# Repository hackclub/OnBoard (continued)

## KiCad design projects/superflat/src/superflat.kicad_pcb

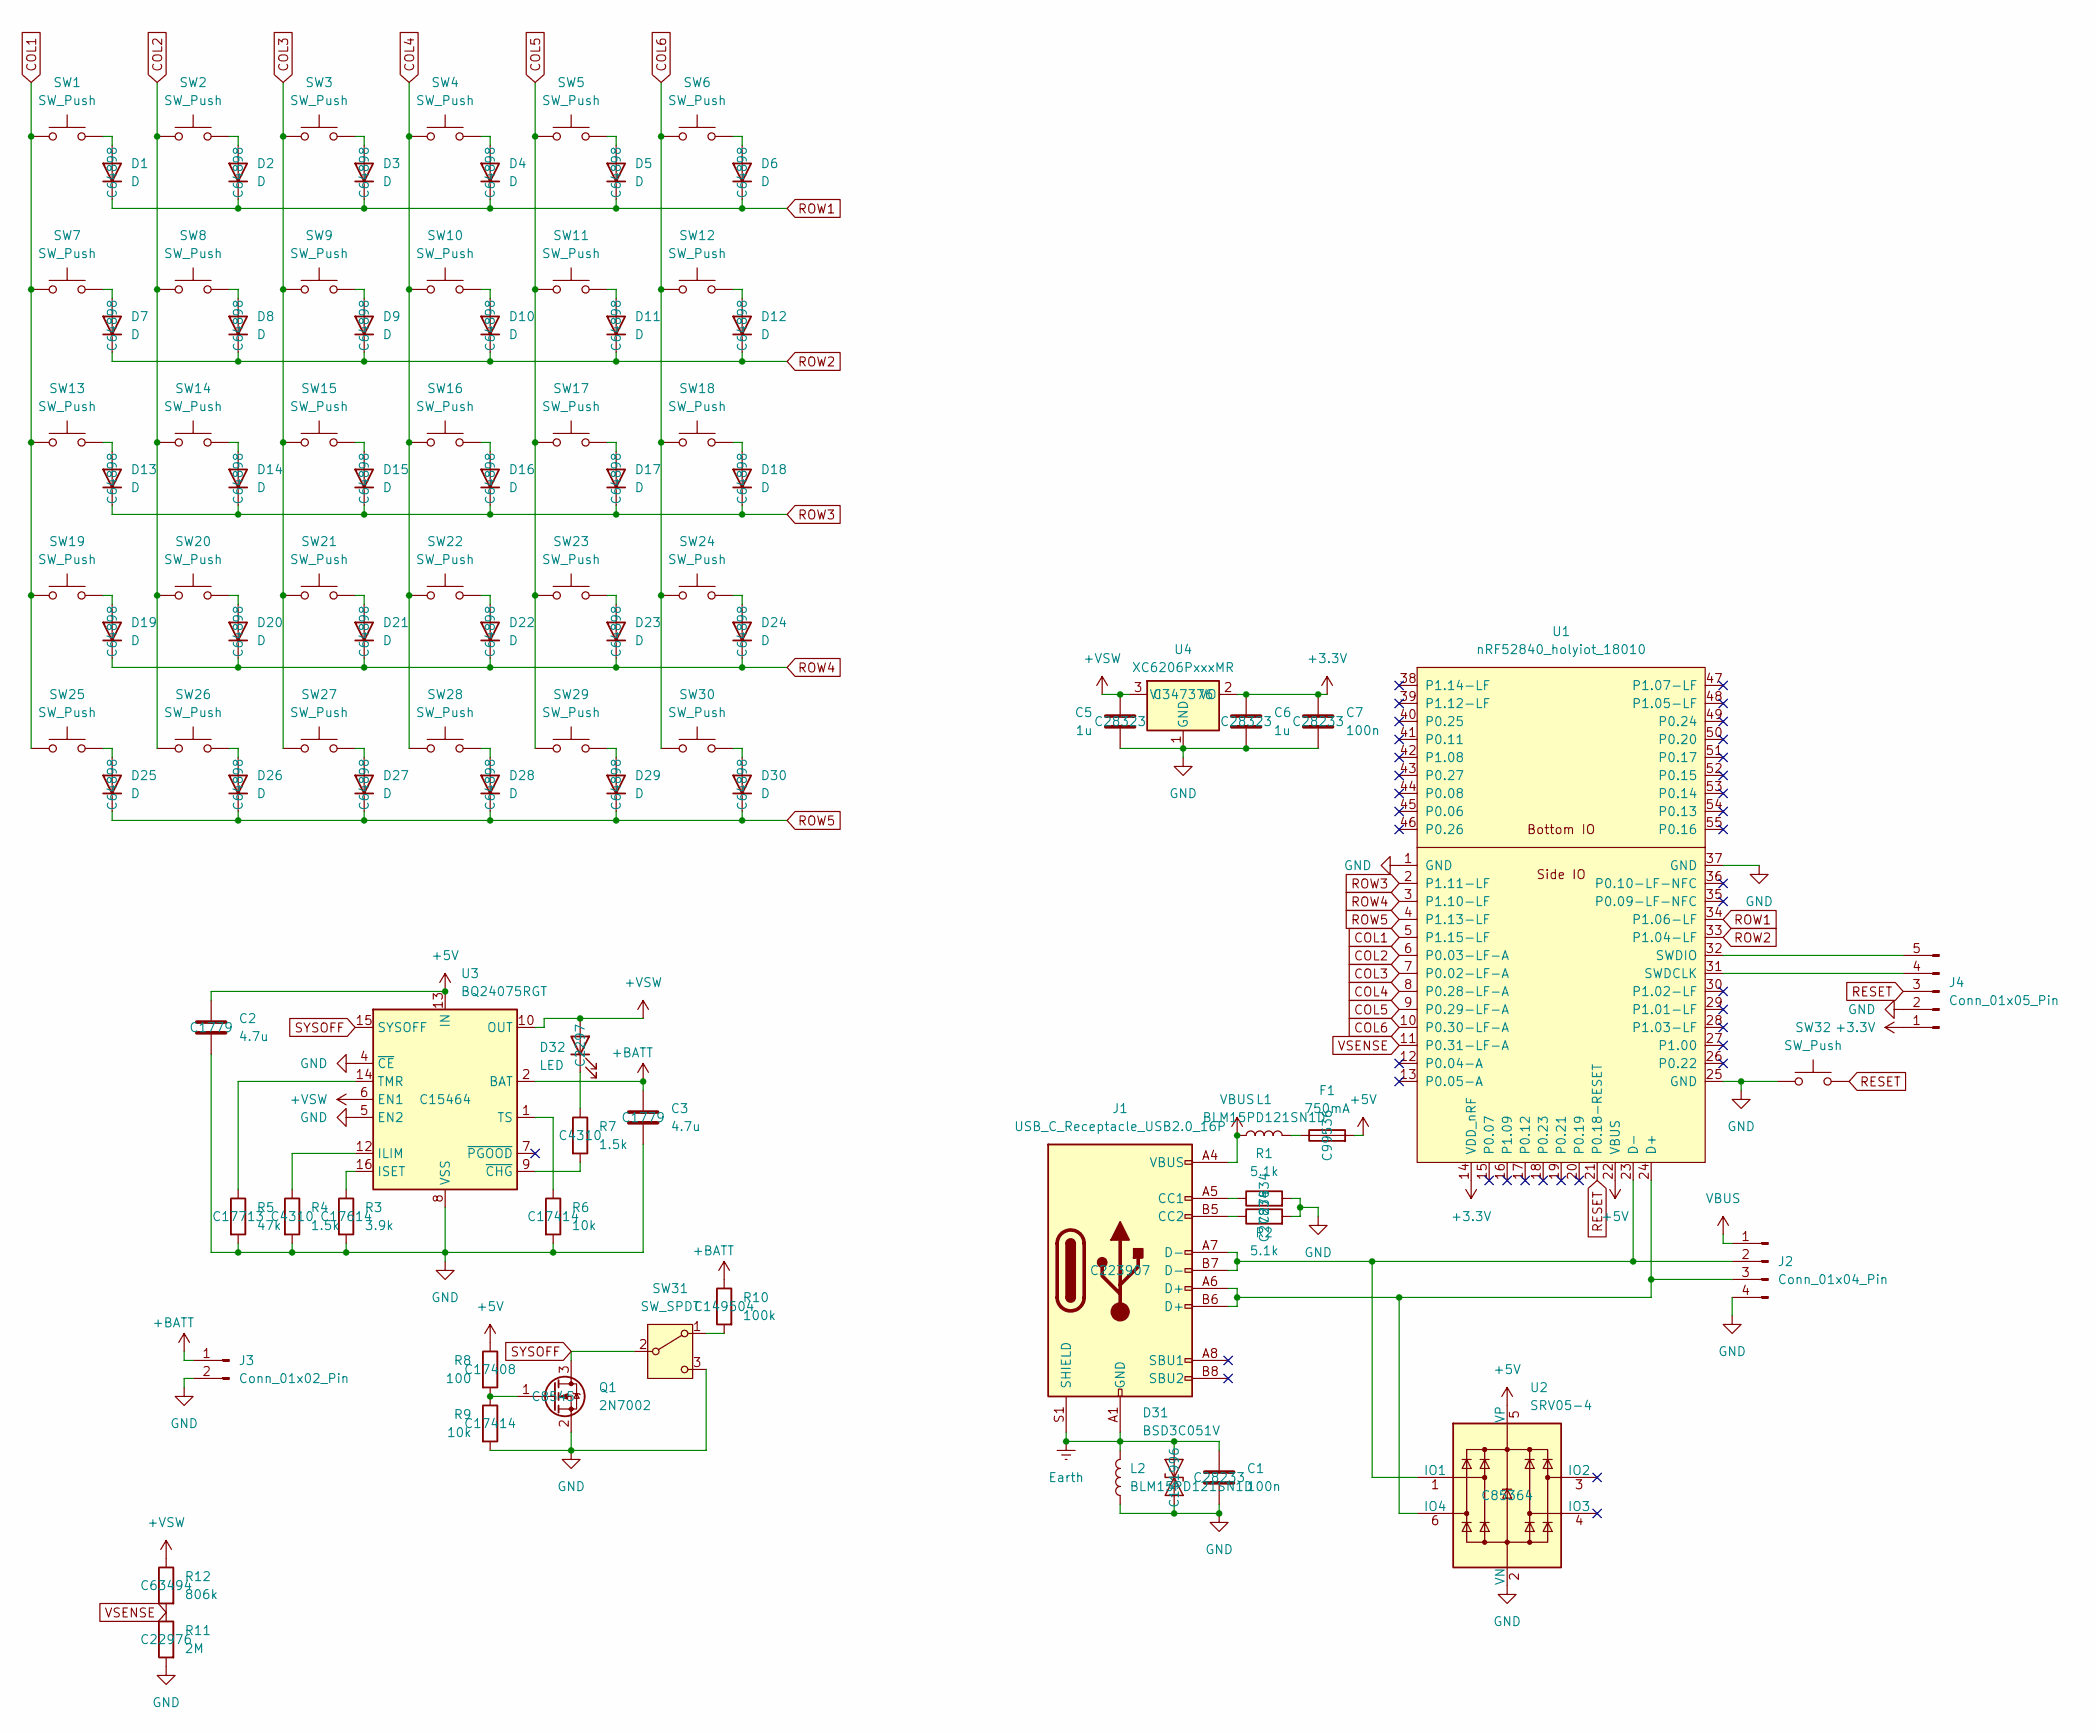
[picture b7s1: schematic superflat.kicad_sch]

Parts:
C1, C7: 100n; C_0805_2012Metric_Pad1.18x1.45mm_HandSolder; LCSC C28233
C2, C3: 4.7u; C_0805_2012Metric_Pad1.18x1.45mm_HandSolder; LCSC C1779
C5, C6: 1u; C_0805_2012Metric_Pad1.18x1.45mm_HandSolder; LCSC C28323
D1, D2, D3, D4, D5, D6, D7, D8, D9, D10, D11, D12, D13, D14, D15, D16, D17, D18, D19, D20, D21, D22, D23, D24, D25, D26, D27, D28, D29, D30: D; D_SOD-123F; LCSC C64898
D31: BSD3C051V; D_SMA; LCSC C151996
D32: LED; LED_0805_2012Metric_Pad1.15x1.40mm_HandSolder; LCSC C2297
F1: 750mA; Fuse_1206_3216Metric_Pad1.42x1.75mm_HandSolder; LCSC C99536
J1: USB_C_Receptacle_USB2.0_16P; USB_C_Receptacle_HRO_TYPE-C-31-M-14; LCSC C223907
J2: Conn_01x04_Pin; PinHeader_1x04_P2.54mm_Vertical
J3: Conn_01x02_Pin; PinHeader_1x02_P2.54mm_Vertical
J4: Conn_01x05_Pin; PinHeader_1x05_P2.54mm_Vertical
L1, L2: BLM15PD121SN1D; L_0402_1005Metric_Pad0.77x0.64mm_HandSolder
Q1: 2N7002; SOT-23; LCSC C8545
R1, R2: 5.1k; R_0805_2012Metric_Pad1.20x1.40mm_HandSolder; LCSC C27834
R3: 3.9k; R_0805_2012Metric_Pad1.20x1.40mm_HandSolder; LCSC C17614
R4, R7: 1.5k; R_0805_2012Metric_Pad1.20x1.40mm_HandSolder; LCSC C4310
R5: 47k; R_0805_2012Metric_Pad1.20x1.40mm_HandSolder; LCSC C17713
R6, R9: 10k; R_0805_2012Metric_Pad1.20x1.40mm_HandSolder; LCSC C17414
R8: 100; R_0805_2012Metric_Pad1.20x1.40mm_HandSolder; LCSC C17408
R10: 100k; R_0805_2012Metric_Pad1.20x1.40mm_HandSolder; LCSC C149504
R11: 2M; R_0603_1608Metric_Pad0.98x0.95mm_HandSolder; LCSC C22976
R12: 806k; R_0805_2012Metric_Pad1.20x1.40mm_HandSolder; LCSC C63494
SW1, SW2, SW3, SW4, SW5, SW6, SW7, SW8, SW9, SW10, SW11, SW12, SW13, SW14, SW15, SW16, SW17, SW18, SW19, SW20, SW21, SW22, SW23, SW24, SW25, SW26, SW27, SW28, SW29, SW30: SW_Push; SW_PG1316S
SW31: SW_SPDT; Slide
SW32: SW_Push; SolderJumper-2_P1.3mm_Open_RoundedPad1.0x1.5mm
U1: nRF52840_holyiot_18010; nRF52840_holyiot_18010_HS_simple
U2: SRV05-4; SOT-23-6-routable; LCSC C85364
U3: BQ24075RGT; VQFN-16-1EP_3x3mm_P0.5mm_EP1.6x1.6mm; LCSC C15464
U4: XC6206PxxxMR; SOT-23-3; LCSC C347376

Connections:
+3.3V: C6.1, C7.1, J4.1, U1.14 (VDD_nRF), U4.2 (VO)
+5V: C2.1, F1.2, R8.1, U1.22 (VBUS), U2.5 (VP), U3.13 (IN)
+BATT: C3.1, J3.1, R10.1, U3.2 (BAT), U3.3 (BAT)
+VSW: C5.1, D32.2 (A), R12.1, U3.6 (EN1), U3.10 (OUT), U3.11 (OUT), U4.3 (VI)
COL1: SW1.1, SW7.1, SW13.1, SW19.1, SW25.1, U1.5 (P1.15-LF)
COL2: SW2.1, SW8.1, SW14.1, SW20.1, SW26.1, U1.6 (P0.03-LF-A)
COL3: SW3.1, SW9.1, SW15.1, SW21.1, SW27.1, U1.7 (P0.02-LF-A)
COL4: SW4.1, SW10.1, SW16.1, SW22.1, SW28.1, U1.8 (P0.28-LF-A)
COL5: SW5.1, SW11.1, SW17.1, SW23.1, SW29.1, U1.9 (P0.29-LF-A)
COL6: SW6.1, SW12.1, SW18.1, SW24.1, SW30.1, U1.10 (P0.30-LF-A)
Earth: C1.1, D31.2 (A2), J1.A1 (GND), J1.A12 (GND), J1.B1 (GND), J1.B12 (GND), J1.S1 (SHIELD), L2.2
GND: C1.2, C2.2, C3.2, C5.2, C6.2, C7.2, D31.1 (A1), J2.4, J3.2, J4.2, L2.1, Q1.2 (S), R1.2, R2.2, R3.2, R4.2, R5.2, R6.2, R9.2, R11.2, SW31.3 (C), SW32.1, U1.1 (GND), U1.25 (GND), U1.37 (GND), U2.2 (VN), U3.4 (~CE), U3.5 (EN2), U3.8 (VSS), U3.17 (VSS), U4.1 (GND)
unnamed: D1.2 (A), SW1.2
unnamed: D2.2 (A), SW2.2
unnamed: D3.2 (A), SW3.2
unnamed: D4.2 (A), SW4.2
unnamed: D5.2 (A), SW5.2
unnamed: D6.2 (A), SW6.2
unnamed: D7.2 (A), SW7.2
unnamed: D8.2 (A), SW8.2
unnamed: D9.2 (A), SW9.2
unnamed: D10.2 (A), SW10.2
unnamed: D11.2 (A), SW11.2
unnamed: D12.2 (A), SW12.2
unnamed: D13.2 (A), SW13.2
unnamed: D14.2 (A), SW14.2
unnamed: D15.2 (A), SW15.2
unnamed: D16.2 (A), SW16.2
unnamed: D17.2 (A), SW17.2
unnamed: D18.2 (A), SW18.2
unnamed: D19.2 (A), SW19.2
unnamed: D20.2 (A), SW20.2
unnamed: D21.2 (A), SW21.2
unnamed: D22.2 (A), SW22.2
unnamed: D23.2 (A), SW23.2
unnamed: D24.2 (A), SW24.2
unnamed: D25.2 (A), SW25.2
unnamed: D26.2 (A), SW26.2
unnamed: D27.2 (A), SW27.2
unnamed: D28.2 (A), SW28.2
unnamed: D29.2 (A), SW29.2
unnamed: D30.2 (A), SW30.2
unnamed: D32.1 (K), R7.1
unnamed: F1.1, L1.2
unnamed: J1.A5 (CC1), R1.1
unnamed: J1.B5 (CC2), R2.1
unnamed: J1.A7 (D-), J1.B7 (D-), J2.2, U1.23 (D-), U2.1 (IO1)
unnamed: J1.A6 (D+), J1.B6 (D+), J2.3, U1.24 (D+), U2.6 (IO4)
unnamed: J4.4, U1.31 (SWDCLK)
unnamed: J4.5, U1.32 (SWDIO)
unnamed: Q1.1 (G), R8.2, R9.1
unnamed: R10.2, SW31.1 (A)
unnamed: R4.1, U3.12 (ILIM)
unnamed: R3.1, U3.16 (ISET)
unnamed: R5.1, U3.14 (TMR)
unnamed: R6.1, U3.1 (TS)
unnamed: R7.2, U3.9 (~CHG)
RESET: J4.3, SW32.2, U1.21 (P0.18-RESET)
ROW1: D1.1 (K), D2.1 (K), D3.1 (K), D4.1 (K), D5.1 (K), D6.1 (K), U1.34 (P1.06-LF)
ROW2: D7.1 (K), D8.1 (K), D9.1 (K), D10.1 (K), D11.1 (K), D12.1 (K), U1.33 (P1.04-LF)
ROW3: D13.1 (K), D14.1 (K), D15.1 (K), D16.1 (K), D17.1 (K), D18.1 (K), U1.2 (P1.11-LF)
ROW4: D19.1 (K), D20.1 (K), D21.1 (K), D22.1 (K), D23.1 (K), D24.1 (K), U1.3 (P1.10-LF)
ROW5: D25.1 (K), D26.1 (K), D27.1 (K), D28.1 (K), D29.1 (K), D30.1 (K), U1.4 (P1.13-LF)
SYSOFF: Q1.3 (D), SW31.2 (B), U3.15 (SYSOFF)
VBUS: J1.A4 (VBUS), J1.A9 (VBUS), J1.B4 (VBUS), J1.B9 (VBUS), J2.1, L1.1
VSENSE: R11.1, R12.2, U1.11 (P0.31-LF-A)

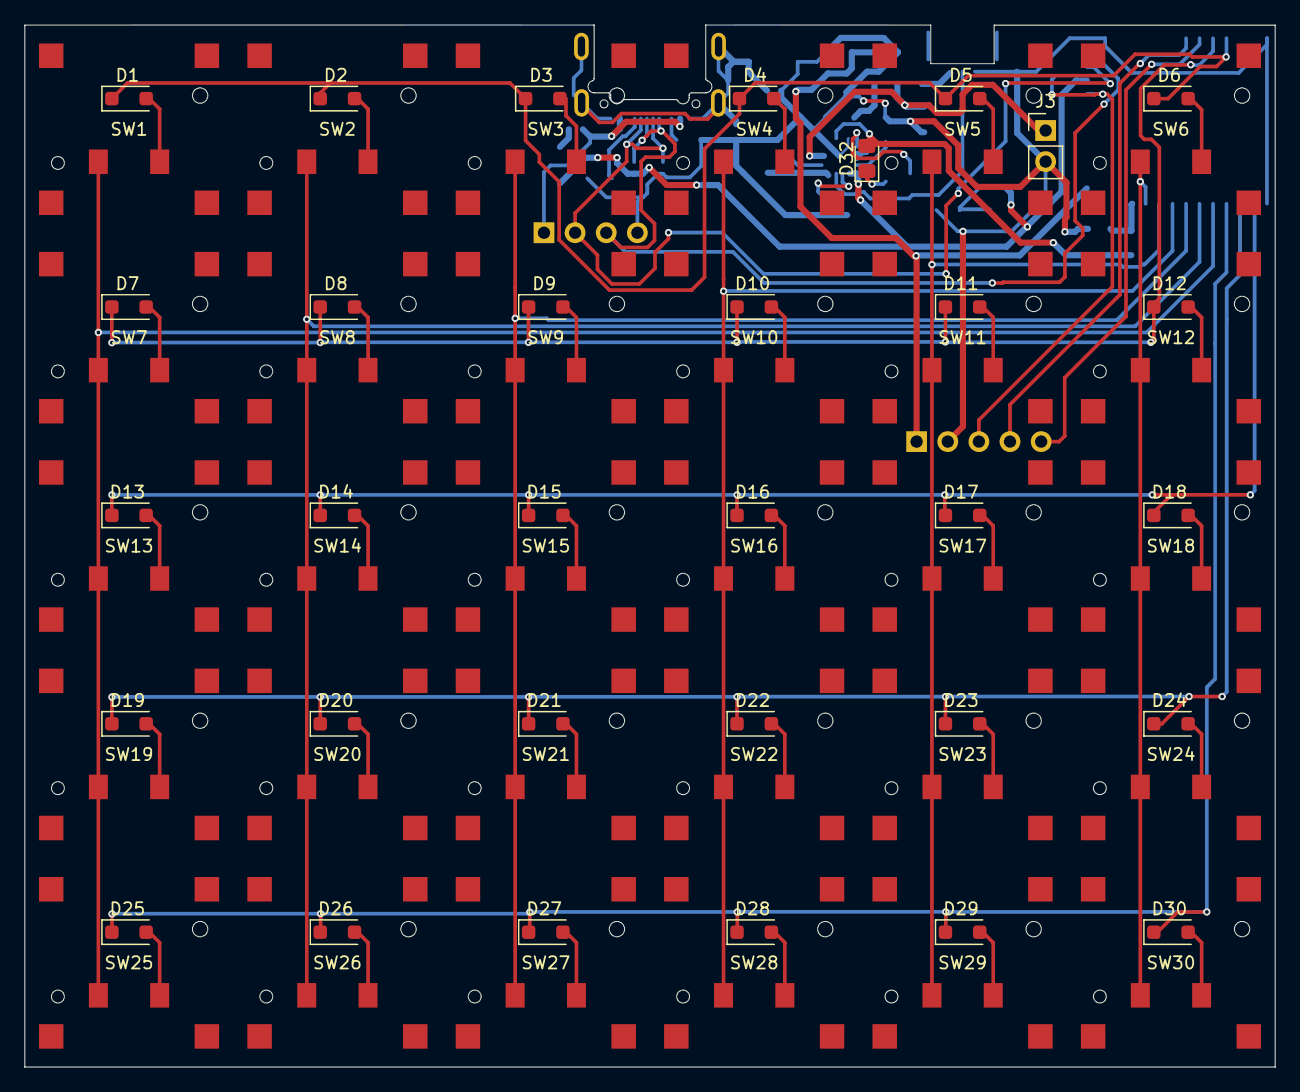
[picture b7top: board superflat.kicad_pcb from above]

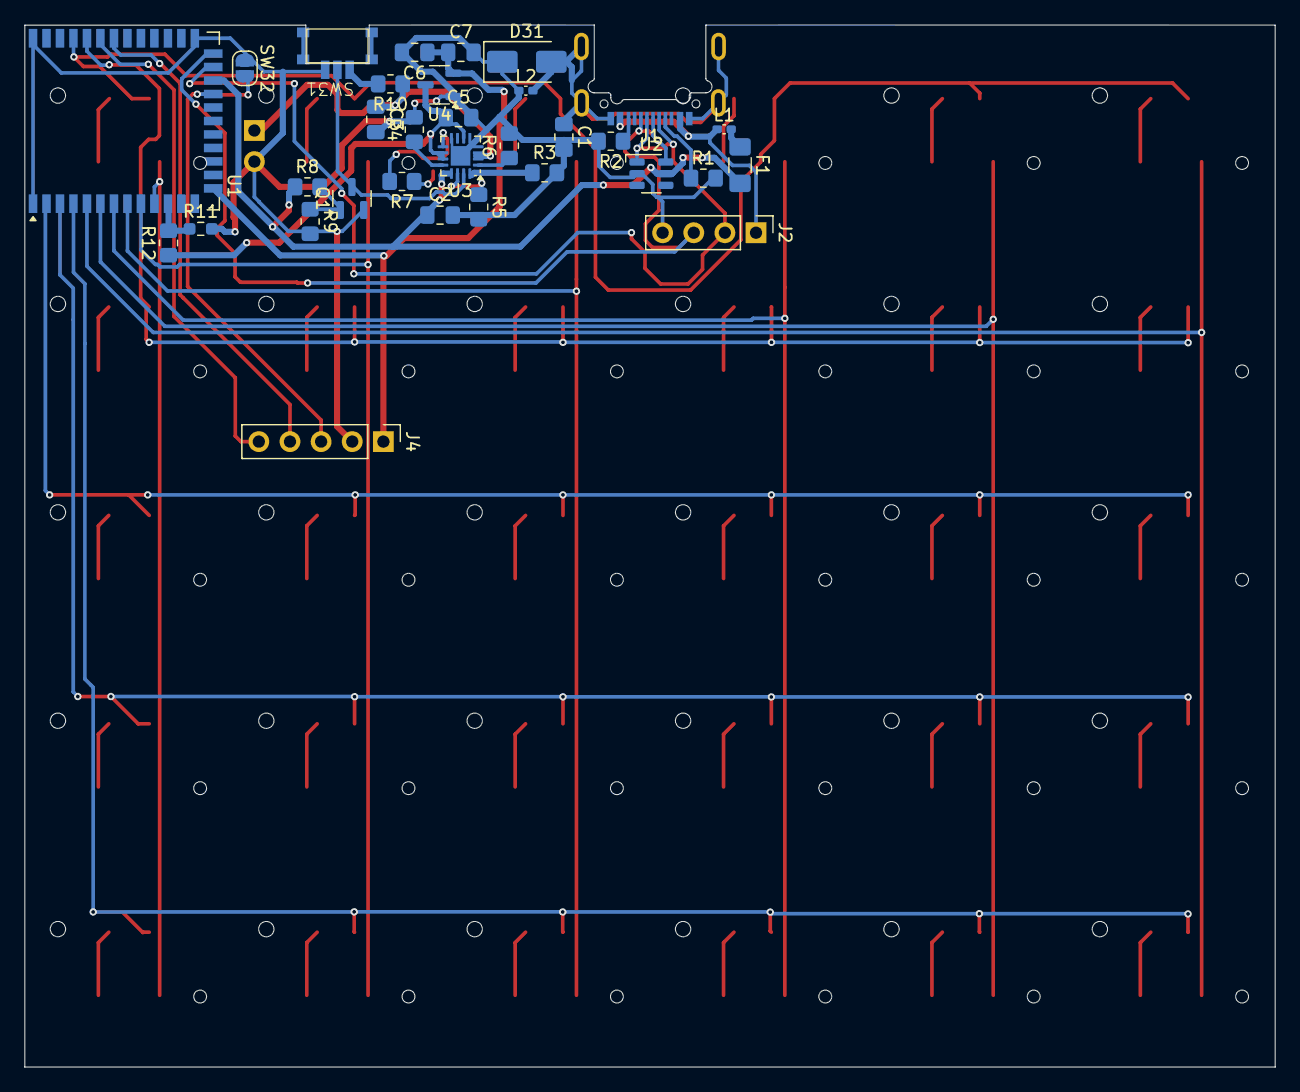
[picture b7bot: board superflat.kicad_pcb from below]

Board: 2 copper layers, 102.0 x 85.0 mm, 94 parts (32 on the bottom side), 66 nets.

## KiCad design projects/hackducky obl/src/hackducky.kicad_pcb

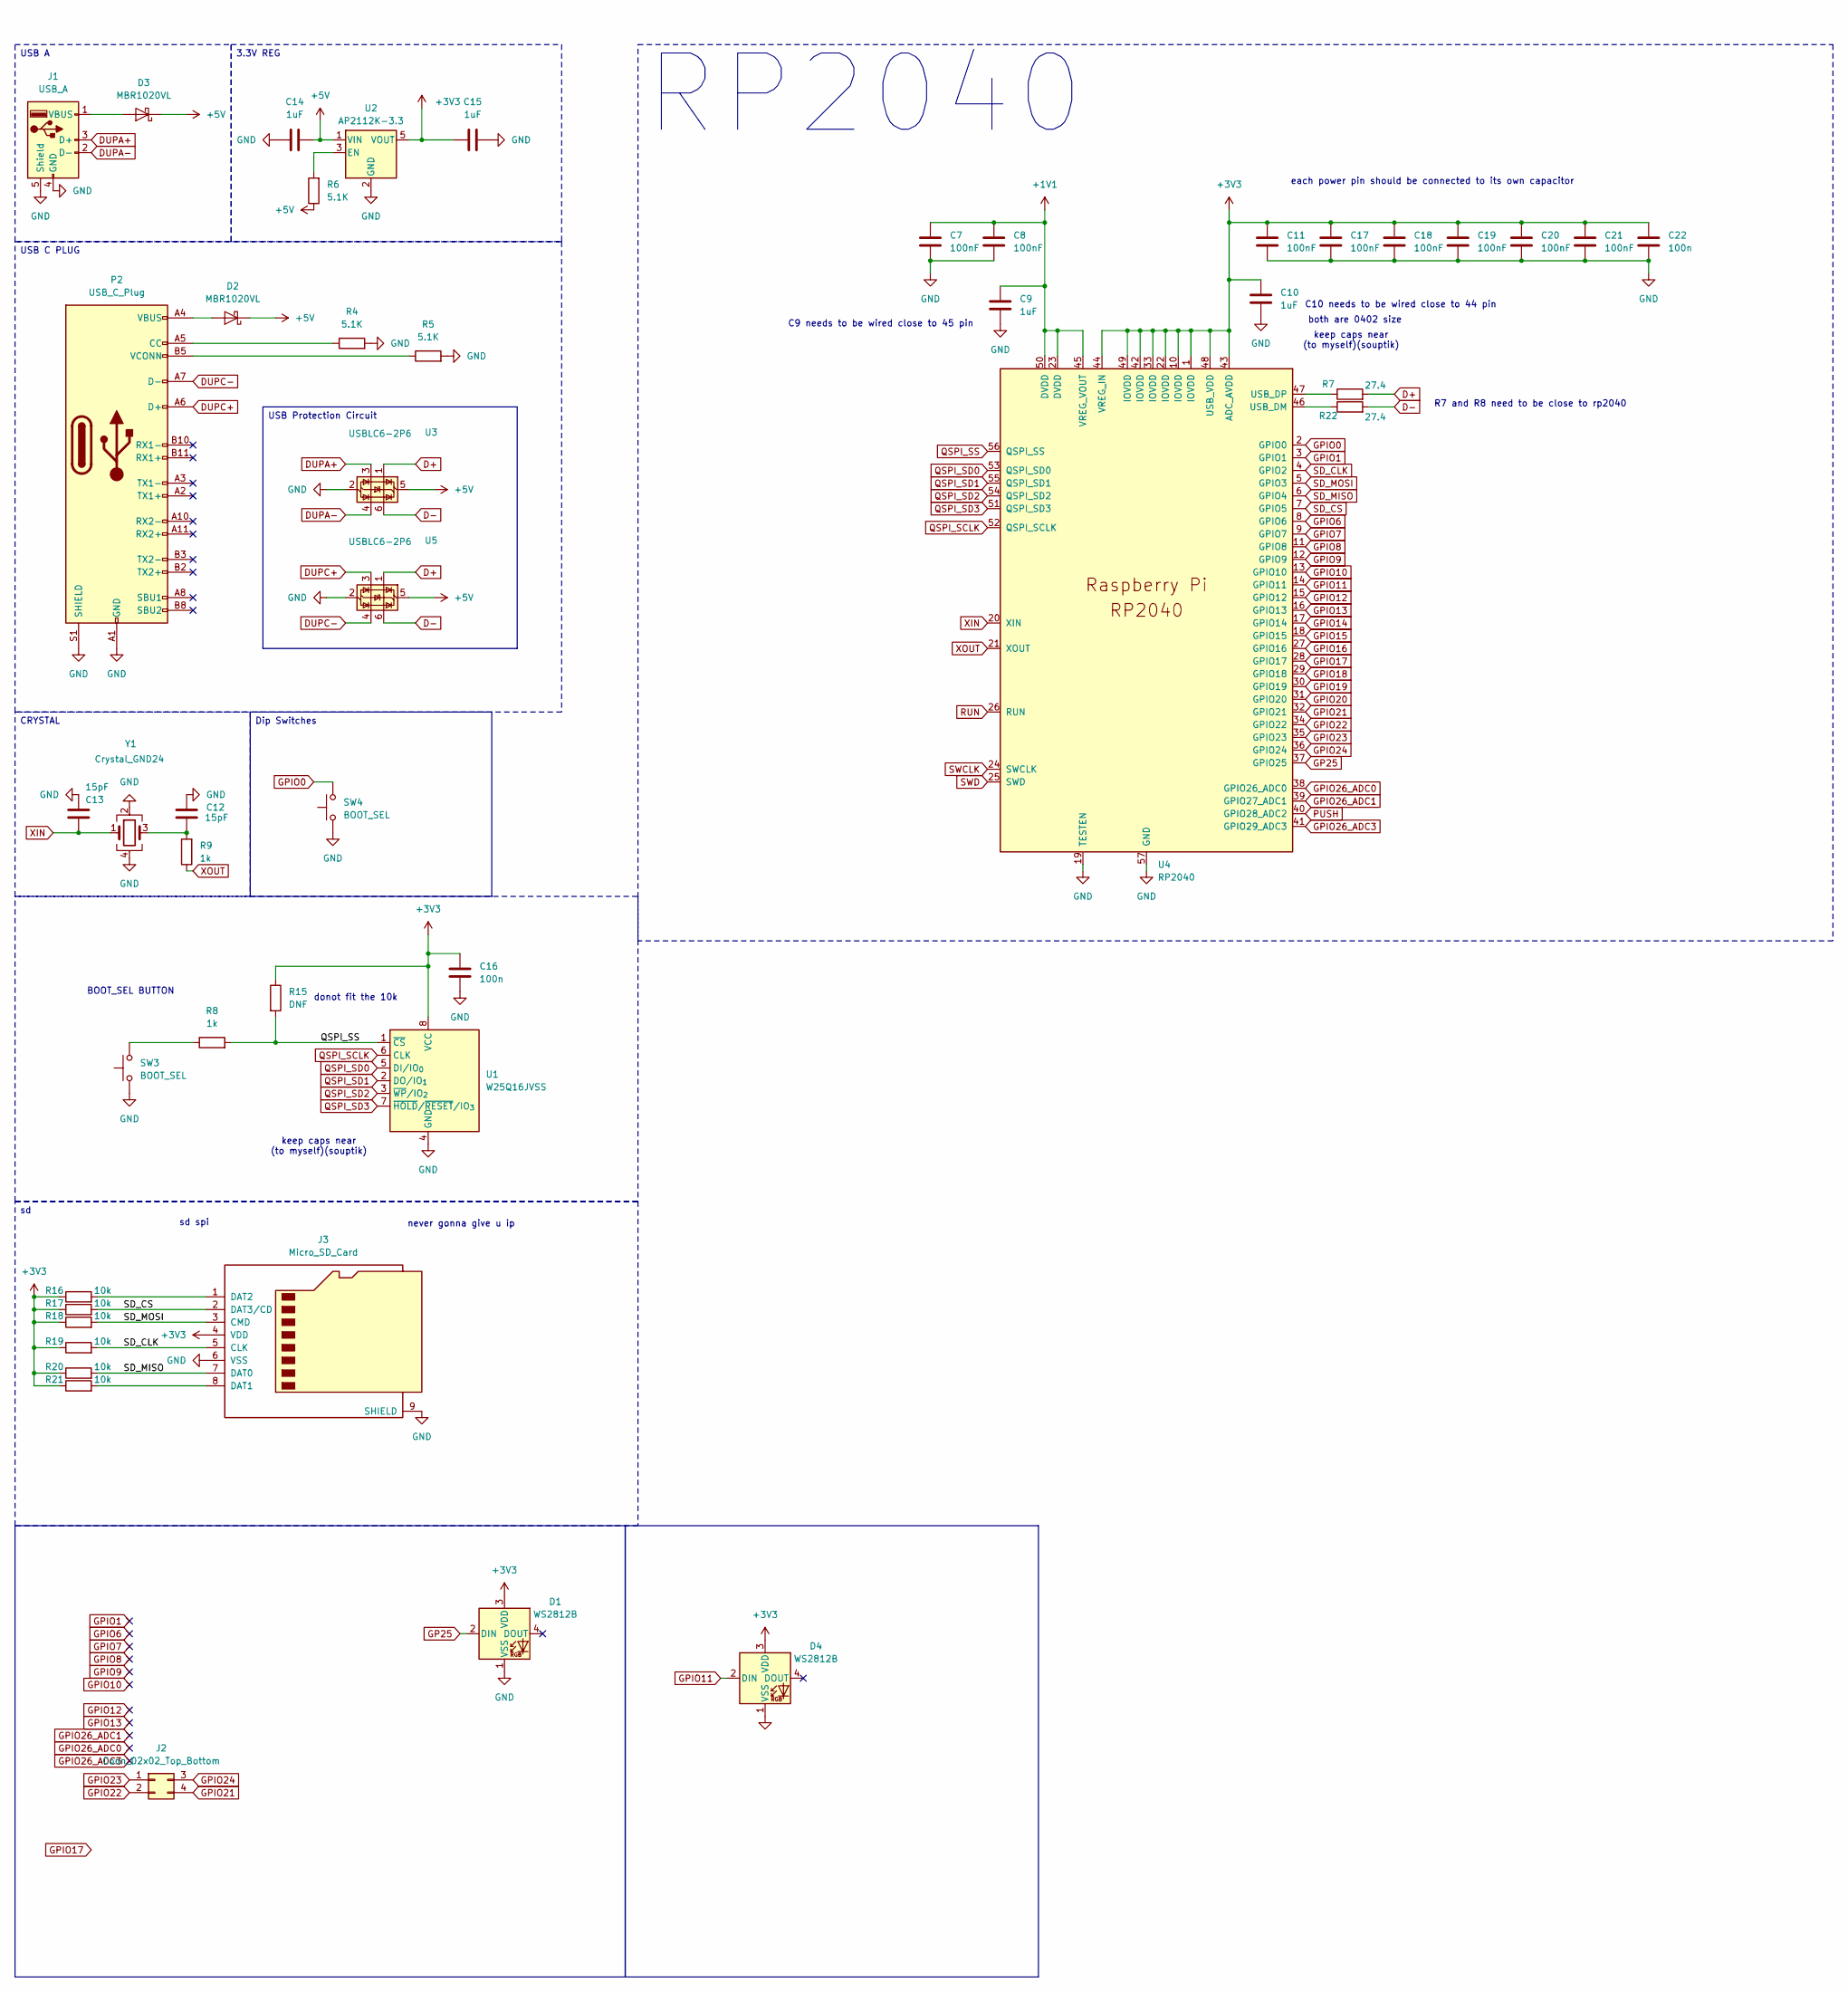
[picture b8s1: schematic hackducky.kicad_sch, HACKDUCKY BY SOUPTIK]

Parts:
C7, C8, C11, C17, C18, C19, C20, C21: 100nF; C_0402_1005Metric
C9, C10, C14: 1uF; C_0402_1005Metric
C12, C13: 15pF; C_0402_1005Metric
C15: 1uF; C_0805_2012Metric
C16, C22: 100n; C_0402_1005Metric
D1, D4: WS2812B; LED_SK6812_EC15_1.5x1.5mm
D2, D3: MBR1020VL; D_SOD-123F
J1: USB_A; USB_A_CNCTech_1001-011-01101_Horizontal
J2: Conn_02x02_Top_Bottom; PinHeader_2x02_P1.00mm_Vertical_SMD
J3: Micro_SD_Card; microSD_HC_Molex_47219-2001
P2: USB_C_Plug; USB_C_Plug_Molex_105444
R4, R5: 5.1K; C_0402_1005Metric
R6: 5.1K; R_0805_2012Metric
R7, R22: 27.4; R_0402_1005Metric
R8, R9: 1k; R_0402_1005Metric
R15: DNF; R_0805_2012Metric_Pad1.20x1.40mm_HandSolder
R16, R17, R18, R19, R20, R21: 10k; R_0402_1005Metric
SW3, SW4: BOOT_SEL; SW_Push_SPST_NO_Alps_SKRK; LCSC C318884
U1: W25Q16JVSS; SOIC-8_5.3x5.3mm_P1.27mm
U2: AP2112K-3.3; SOT-23-5
U3, U5: USBLC6-2P6; SOT-666
U4: RP2040; QFN-56-1EP_7x7mm_P0.4mm_EP3.2x3.2mm
Y1: Crystal_GND24; Crystal_SMD_Abracon_ABM8G-4Pin_3.2x2.5mm

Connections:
+1V1: C7.1, C8.1, C9.1, U4.23 (DVDD), U4.45 (VREG_VOUT), U4.50 (DVDD)
+3V3: C10.1, C11.1, C15.2, C16.1, C17.1, C18.1, C19.1, C20.1, C21.1, C22.1, D1.3 (VDD), D4.3 (VDD), J3.4 (VDD), R15.1, R16.1, R17.1, R18.1, R19.1, R20.1, R21.1, U1.8 (VCC), U2.5 (VOUT), U4.1 (IOVDD), U4.10 (IOVDD), U4.22 (IOVDD), U4.33 (IOVDD), U4.42 (IOVDD), U4.43 (ADC_AVDD), U4.44 (VREG_IN), U4.48 (USB_VDD), U4.49 (IOVDD)
+5V: C14.1, D2.1 (K), D3.1 (K), R6.1, U2.1 (VIN), U3.5 (VBUS), U5.5 (VBUS)
D+: R7.2, U3.1 (I/O1), U5.1 (I/O1)
D-: R22.2, U3.6 (I/O1), U5.6 (I/O1)
DUPA+: J1.3 (D+), U3.3 (I/O2)
DUPA-: J1.2 (D-), U3.4 (I/O2)
DUPC+: P2.A6 (D+), U5.3 (I/O2)
DUPC-: P2.A7 (D-), U5.4 (I/O2)
GND: C7.2, C8.2, C9.2, C10.2, C11.2, C12.2, C13.2, C14.2, C15.1, C16.2, C17.2, C18.2, C19.2, C20.2, C21.2, C22.2, D1.1 (VSS), D4.1 (VSS), J1.4 (GND), J1.5 (Shield), J3.6 (VSS), J3.9 (SHIELD), P2.A1 (GND), P2.A12 (GND), P2.B1 (GND), P2.B12 (GND), P2.S1 (SHIELD), R4.2, R5.2, SW3.1, SW4.1, U1.4 (GND), U2.2 (GND), U3.2 (GND), U4.19 (TESTEN), U4.57 (GND), U5.2 (GND), Y1.2, Y1.4
GP25: D1.2 (DIN), U4.37 (GPIO25)
GPIO0: SW4.2, U4.2 (GPIO0)
GPIO1: U4.3 (GPIO1)
GPIO6: U4.8 (GPIO6)
GPIO7: U4.9 (GPIO7)
GPIO8: U4.11 (GPIO8)
GPIO9: U4.12 (GPIO9)
GPIO10: U4.13 (GPIO10)
GPIO11: D4.2 (DIN), U4.14 (GPIO11)
GPIO12: U4.15 (GPIO12)
GPIO13: U4.16 (GPIO13)
GPIO14: U4.17 (GPIO14)
GPIO15: U4.18 (GPIO15)
GPIO16: U4.27 (GPIO16)
GPIO17: U4.28 (GPIO17)
GPIO18: U4.29 (GPIO18)
GPIO19: U4.30 (GPIO19)
GPIO20: U4.31 (GPIO20)
GPIO21: J2.4, U4.32 (GPIO21)
GPIO22: J2.2, U4.34 (GPIO22)
GPIO23: J2.1, U4.35 (GPIO23)
GPIO24: J2.3, U4.36 (GPIO24)
GPIO26_ADC0: U4.38 (GPIO26_ADC0)
GPIO26_ADC1: U4.39 (GPIO27_ADC1)
GPIO26_ADC3: U4.41 (GPIO29_ADC3)
unnamed: C12.1, R9.2, Y1.3
unnamed: D2.2 (A), P2.A4 (VBUS), P2.A9 (VBUS), P2.B4 (VBUS), P2.B9 (VBUS)
unnamed: D3.2 (A), J1.1 (VBUS)
unnamed: J3.8 (DAT1), R21.2
unnamed: J3.1 (DAT2), R16.2
unnamed: P2.A5 (CC), R4.1
unnamed: P2.B5 (VCONN), R5.1
unnamed: R8.1, SW3.2
unnamed: R6.2, U2.3 (EN)
unnamed: R22.1, U4.46 (USB_DM)
unnamed: R7.1, U4.47 (USB_DP)
PUSH: U4.40 (GPIO28_ADC2)
QSPI_SCLK: U1.6 (CLK), U4.52 (QSPI_SCLK)
QSPI_SD0: U1.5 (DI/IO_{0}), U4.53 (QSPI_SD0)
QSPI_SD1: U1.2 (DO/IO_{1}), U4.55 (QSPI_SD1)
QSPI_SD2: U1.3 (~WP/IO_{2}), U4.54 (QSPI_SD2)
QSPI_SD3: U1.7 (~HOLD/~RESET/IO_{3}), U4.51 (QSPI_SD3)
QSPI_SS: R8.2, R15.2, U1.1 (~CS), U4.56 (QSPI_SS)
RUN: U4.26 (RUN)
SD_CLK: J3.5 (CLK), R19.2, U4.4 (GPIO2)
SD_CS: J3.2 (DAT3/CD), R17.2, U4.7 (GPIO5)
SD_MISO: J3.7 (DAT0), R20.2, U4.6 (GPIO4)
SD_MOSI: J3.3 (CMD), R18.2, U4.5 (GPIO3)
SWCLK: U4.24 (SWCLK)
SWD: U4.25 (SWD)
XIN: C13.1, U4.20 (XIN), Y1.1
XOUT: R9.1, U4.21 (XOUT)

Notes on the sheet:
sd spi
C9 needs to be wired close to 45 pin
keep caps near (to myself)(souptik)
donot fit the 10k
R7 and R8 need to be close to rp2040
C10 needs to be wired close to 44 pin
BOOT_SEL BUTTON
never gonna give u ip
both are 0402 size
each power pin should be connected to its own capacitor
CRYSTAL
RP2040
USB Protection Circuit
USB C PLUG
Dip Switches
3.3V REG
USB A

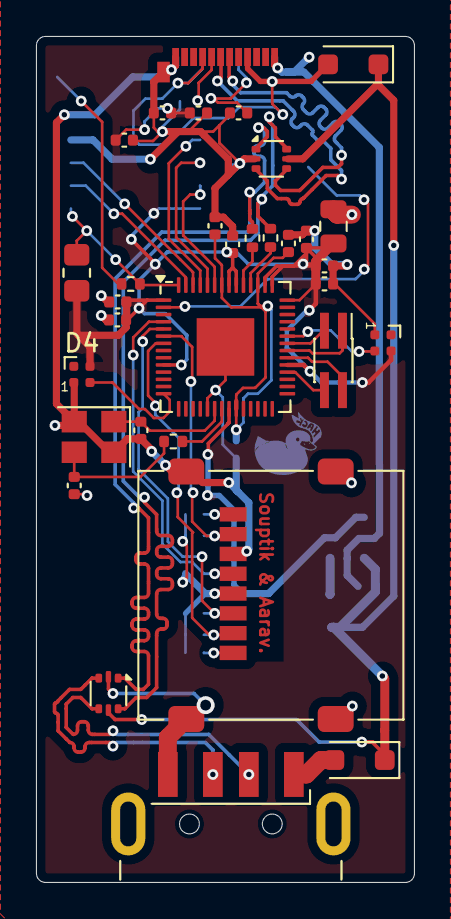
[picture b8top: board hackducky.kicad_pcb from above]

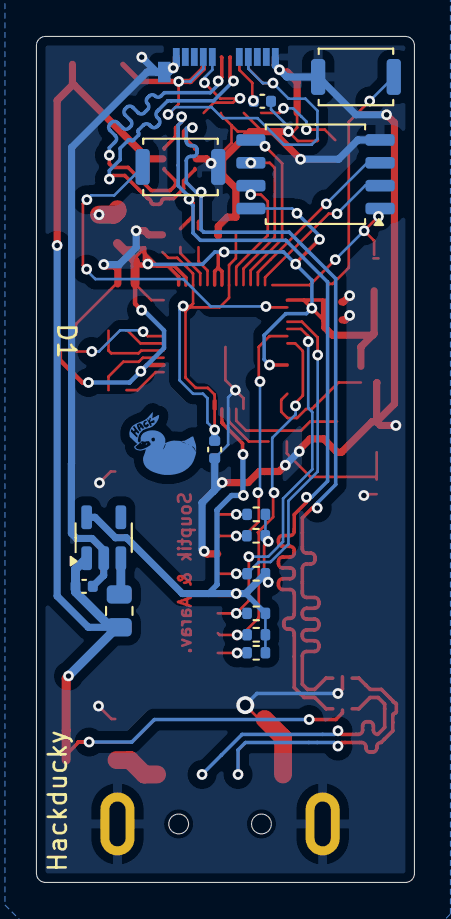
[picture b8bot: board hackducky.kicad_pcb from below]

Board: 2 copper layers, 21.0 x 47.0 mm, 46 parts (14 on the bottom side), 40 nets.

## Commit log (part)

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2025-04-19 Horizon_Orbit (#1697)
    * Create README.md
    * Add files via upload
    * Create a
    * Add files via upload
    * Delete projects/Horizon_Orbit/src/a
2025-04-19 add toby's raver
2025-04-19 Update existing tobydio board (#1696)
    * update tobydio board errors
    * update tobydio board
2025-04-19 ControlPad (#1693)
    * Create README.md
    * Update README.md
    * Update README.md
    * Update README.md
    * Add files via upload
    * Rename Gerber_ControlPad.zip to gerber.zip
2025-04-19 Rename projects/Yoav_Mlotok_Business_Card/yoav-mlotok-card.epro to projects/Yoav_Mlotok_Business_Card/src/project.epro
2025-04-20 Add uSDReader
2025-04-20 Owais_school_card (#1687)
    * Create owais-school-thingy
    * Create README.md
    * Update README.md
    * Add files via upload
    * Create README.md
    * Add files via upload
2025-04-20 feat: update megapad design and schematic
2025-04-20 add my own project
2025-04-20 Add schematic
2025-04-20 Add files via upload
    this is a project to use the rest of the 5$ in my onboard hcb card
2025-04-20 create src/
2025-04-20 Add kicad editor files
2025-04-20 add cart images
2025-04-20 update costs
2025-04-20 Dav-Hub (#1699)
    * Create readme.md
    * Add files via upload
    * Rename readme.md to README.md
    * Add files via upload
    * Update README.md
    ---------
2025-04-20 Add uSDReader (#1702)
2025-04-20 Add Ayaan's NFC Tag (#1700)
    * Create README.md
    * Update README.md
    * Update README.md
    * Add files via upload
    * Add files via upload
    * Update README.md
2025-04-20 SaltyMold-Card (#1546)
    * Create README.md
    * Create README.md
    * Add files via upload
    * Delete projects/NFC SaltyMold directory
    * Update README.md
    * Rename commande.png to cart.png
2025-04-20 change to minimum order size
2025-04-20 update prices
2025-04-20 added (hopefully) all required files
2025-04-20 Created Yoav Mlotok's project (#1701)
    * Create README.md
    * Add files via upload
    * Add files via upload
    * Add files via upload
    * Rename projects/Yoav_Mlotok_Business_Card/yoav-mlotok-card.epro to projects/Yoav_Mlotok_Business_Card/src/project.epro
2025-04-20 Create hello
2025-04-20 Rename Screenshot 2025-04-20 193452.png to cart.png
2025-04-21 protoboard (#1681)
    * Create readme.md
    * Add files via upload
    * Delete projects/protoboard/gerber.zip
    * Add files via upload
    * Delete projects/protoboard/src/pcb.json
    * Add files via upload
2025-04-21 Onboard Grant (#1707)
    * Create readme.md
    * Add files via upload
2025-04-21 title (#1708)
    * Create readme.md
    * Add files via upload
2025-04-21 Andreas-usb (#1691)
    * Create readme.md
    * Add files via upload
    * Rename readme.md to README.md
    * Delete projects/Usb-Hub/src/PCB.json
    * Delete projects/Usb-Hub/schematic.pdf
    * Delete projects/Usb-Hub/gerber.zip
2025-04-21 Add PCB art to use the rest of 5$ in my onboard hcb (#1703)
    * Add files via upload
    * Delete projects/reversible split keyboard/price.png
    * Delete projects/reversible split keyboard/Gerbers.zip
    * Add files via upload
    * Add files via upload
    * Delete projects/reversible split keyboard/reversible.kicad_pcb
2025-04-22 EEPROM Programmer (#1709)
    * Create README.md
    * Update README.md
    * Add files via upload
    * Add files via upload
    * Add files via upload
    * Add files via upload
2025-04-22 Rename Schematic_learningpcb_2025-04-21.pdf to schematic.pdf
2025-04-22 Rename image_2025-04-21_222704961.png to cart.png
2025-04-22 Rename Gerber_learningpcb_PCB_learningpcb_2025-04-21.zip to gerber.zip
2025-04-22 Rename gerber (2).zip to gerber.zip
2025-04-22 Rename schematic (1).pdf to schematic.pdf
2025-04-22 USB-C (#1712)
    * Create readme.md
    * Add files via upload
    * Rename gerber (2).zip to gerber.zip
    * Rename schematic (1).pdf to schematic.pdf
2025-04-23 added src
2025-04-23 added config.yaml
2025-04-23 SD-Card (#1711)
    * Create readme.md
    * Add files via upload
    * Update and rename Pcb.json to Pcb.json
    * Update and rename Schematic.json to Schematic.json
2025-04-23 Rename Hackpad.pdf to schematic.pdf
2025-04-23 added files
2025-04-23 [No grant needed] Update megapad schematic and gerber files (#1716)
2025-04-23 Rename cap.pdf to schematic.pdf
2025-04-23 Rename gerber (3).zip to gerber.zip
2025-04-23 Rename Schematic_fuelsensor_2025-04-23.pdf to schematic.pdf
2025-04-23 Add Calculusulator (#1689)
    * Create README.md
    * Update README.md
    * Update README.md
    * Create placeholder
    * Delete projects/Calculusulator/src/placeholder
    * Create placeholder
2025-04-23 yapyapyapyap
2025-04-23 very skibidi
2025-04-24 grant pls!!
2025-04-25 Update VENDORS.md added elecrow pcba service (#1652)
2025-04-25 tanisha_in_space (#1722)
    * Create readme.md
    * Add files via upload
    * Add files via upload
    * Delete projects/tanisha_in_space/cart.png.png
    * Add files via upload
2025-04-25 fuel_sensor (#1720)
    * Create readme.md
    * Add files via upload
    * Rename gerber (3).zip to gerber.zip
    * Update and rename projects/fuel_sensor/PCB_PCB_fuelsensor_2025-04-23.json to projects/fuel_sensor/src/PCB.json
    * Update and rename projects/fuel_sensor/SCH_fuelsensor_2025-04-23.json to projects/fuel_sensor/src/SCH.json
    * Rename Schematic_fuelsensor_2025-04-23.pdf to schematic.pdf
2025-04-25 skib (#1721)
    * yapyapyapyap
    * very skibidi
2025-04-25 MemoryBoard (#1718)
    * Create readme.md
    * Add files via upload
2025-04-25 adding project QPD_AMPLIFIER (#1705)
    * Create README.md
    * Update README.md
    * Update README.md
    * added (hopefully) all required files
2025-04-25 Onboard PCB macroboard (#1719)
    * Create readme.md
    * Add files via upload
2025-04-25 Rename projects/gerber.zip to projects/andreascard/gerber.zip
2025-04-25 Rename projects/schematic.pdf to projects/andreascard/schematic.pdf
2025-04-25 Rename projects/image_2025-04-23_170456454.png to projects/andreascard/cart.png
2025-04-25 Rename Gerber_claprelay_pcb_2025-04-26.zip to gerber.zip
2025-04-25 Rename image_2025-04-26_003502681.png to cart.png
2025-04-25 Rename Schematic_claprelay_2025-04-26.pdf to schematic.pdf
2025-04-26 Lucy's PCB is HOT, HOT, HOT!
2025-04-27 Rename odyssey.gbr.zip to gerber.zip
2025-04-27 Rename odyssey.pdf to schematic.pdf
2025-04-27 Hewis_CArd (#1723)
    * Create hello
    * Add files via upload
    * Create readme.md
    * Delete projects/hewis_hacker_card/src/hello
    * Add files via upload
    * Rename Screenshot 2025-04-20 193452.png to cart.png
2025-04-27 odysseymain (#1728)
    * Create README.md
    * Update README.md
    * Add files via upload
    * Create test.md
    * Add files via upload
    * Rename odyssey.gbr.zip to gerber.zip
2025-04-27 Lucy's PCB (#1727)
    Lucy's PCB is HOT, HOT, HOT!
2025-04-27 add clap relay project (#1726)
    * Create readme.md
    * Add files via upload
    * Rename Gerber_claprelay_pcb_2025-04-26.zip to gerber.zip
    * Rename image_2025-04-26_003502681.png to cart.png
    * Rename Schematic_claprelay_2025-04-26.pdf to schematic.pdf
    * Update and rename projects/claprelaymodule/SCH_claprelay_2025-04-26.json to projects/claprelaymodule/src/sch.json
2025-04-27 PLS add trufflesyt/onboard (#1725)
    grant pls!!
2025-04-27 Pull request for Layan's DJ Controller (#1715)
    * Create README.md
    * Add files via upload
    * Rename Hackpad.pdf to schematic.pdf
    * added files
2025-04-27 Create dummy
2025-04-27 Max's Charlieplexed Matrix! (#1704)
    * add my own project
    * Add schematic
    * create src/
    * Add kicad editor files
    * add cart images
    * update costs
2025-04-27 Rename {BD718A0A-87D1-4BF1-A4F7-5F7D5730A019}.png to cart
2025-04-27 Rename cart to cart.png
2025-04-27 Rename Gerber.zip to gerber.zip
2025-04-27 Create
2025-04-27 Create file
2025-04-28 Rename Screenshot 2025-04-28 185815.png to cart.png
2025-04-29 Rename projects/PCB-fethead/cart.png to projects/PCB-fethead/src/cart.png
2025-04-29 Rename projects/PCB-fethead/src/cart.png to projects/PCB-fethead/cart.png
2025-04-29 e (#1724)
2025-05-02 Create src
2025-05-02 Rename Schematic.pdf to schematic.pdf
2025-05-03 Create e
2025-05-03 Rename JLCPCB.png to cart.png
2025-05-03 added end
2025-05-03 heading h2
2025-05-03 Onboard ended (#1738)
    * RGB_C
    * Delete projects/rgb_strip_controller/src/fp-info-cache
    * Add files via upload
    * Update README.md
    * Update README.md
    * added end
2025-05-03 fix (#1739)
    * RGB_C
    * Delete projects/rgb_strip_controller/src/fp-info-cache
    * Add files via upload
    * Update README.md
    * Update README.md
    * added end
2025-05-03 fix (#1739) (#1740)
    * RGB_C
    * Delete projects/rgb_strip_controller/src/fp-info-cache
    * Add files via upload
    * Update README.md
    * Update README.md
    * added end
2025-05-03 Rename projects/a3acx_hacker_card/PCB_NFC Card.json to projects/a3acx_hacker_card/src/pcb.json
2025-05-03 Rename projects/a3acx_hacker_card/NFC Card.json to projects/a3acx_hacker_card/src/schematic.json
2025-05-04 Add Icepi Zero
2025-05-05 Create README.md (#1745)
    * Create README.md
    * Add files via upload
    * Create src
    * Delete projects/Neha NFC Card/src
    * Create .gitkeep
    * Add files via upload
2025-05-05 ODOMETER!!!!!!!! (#1733)
    * Create README.md
    * Update README.md
    * Add files via upload
    * Add files via upload
    * Add files via upload
    * Add files via upload
2025-05-05 Added src folder
2025-05-06 Smart Ring added
2025-05-06 testing
2025-05-06 Business Card Thingy (#1729)
    * Create README.md
    * Update README.md
    * Add files via upload
    * Create dummy
    * Add files via upload
    * Update README.md
2025-05-08 Add all files related to smart-ring
2025-05-08 Rename cart.png.png to cart.png
2025-05-08 Smart Ring (#1748)
    * Add all files related to smart-ring
    * Rename cart.png.png to cart.png
2025-05-09 Rename cart.PNG to cart.png
2025-05-09 Rename gerber.zip.zip to gerber.zip
2025-05-10 Herculus Bat C HUB (#1731)
    * Create readme.md
    * Create hello
    * Add files via upload
    * Rename Screenshot 2025-04-28 185815.png to cart.png
    * Add files via upload
    * Add files via upload
2025-05-10 Miku NFC Key Chain (#1742)
    * Create README.md
    * Add files via upload
    * Rename Capture.PNG to cart.png
    * Rename Gerber_Hacker-Card_PCB_Hacker-Card_2024-09-23.zip to gerber.zip
    * Add files via upload
    * Rename Schematic_Hacker-Card_2024-09-23.pdf to schematic.pdf
2025-05-15 Create Abhinav's Business Card
2025-05-15 Rename Abhinav Schematic May 15 2025.pdf to schematic.pdf
2025-05-16 Rename projects/Abhinav's PCB Card/Abhinav Schematic May 15 2025.json to projects/Abhinav's PCB Card/src/schematic.json
2025-05-16 Rename Abhinav Schematic May 15 2025 (1).json to pcb.json
2025-05-16 Rename gerber-2.zip to gerber.zip
2025-05-17 Create projects123
2025-05-17 Create conors nfc card
2025-05-17 Rename conors nfc card to conors-nfc-card.md
2025-05-24 added card.png
2025-05-25 Home Assistant Control pad
2025-05-25 cart
2025-05-25 fix folder name
2025-05-27 submit esp-streamer (#1730)
    * Create README.md
    * Add files via upload
    * Create
    * Delete projects/esp-streamer/src
    * Create file
    * Add files via upload
2025-05-27 Ultra USB Hub (#1735)
    * Create README.md
    * Add files via upload
    * Add files via upload
    * Create useless.txt
    * Add files via upload
    * Delete projects/ultra_usb_hub/schematic.json
2025-05-27 Add files via upload
    all the stuff
2025-05-27 Rename BOM_cool_thing_2025-05-27.csv to BOM.csv
2025-05-27 Rename PickAndPlace_PCB_cool_thing_2025-05-27.csv to PickAndPlace.csv
2025-05-27 Rename Schematic_cool_thing_2025-05-27.pdf to Schematic.pdf
2025-05-27 Rename Gerber_cool_thing_PCB_cool_thing_2025-05-27.zip to gerber.zip
2025-05-27 easy eda files😔
2025-05-28 final commit
2025-05-29 Rename Screenshot 2025-05-28 141100.png to cart.png
